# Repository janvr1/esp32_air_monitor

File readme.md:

### TO-DO:
* (SW) Ubidots

### Notes:
* GPIO 6-11: SPI flash
* GPIO 16-17: PSRAM
* GPIO 34-39: Input only
* EWMA filter: alpha = 2\*pi\*fc\*Ts/(1+2\*pi\*fc\*Ts)

### Display timings:
* F_pwm = 312,5 kHz (T=3,2 us)
* PWM: T_low@100%duty=~20 ns
* T_transfer = ~22 us (2 rows of 64 pixels * 3 colors)
* T_row = 200 us (T_transfer + 178 delay)
* Minimum brightness: T_on = 22 us (transfer time), T_off = 178 us (178 us delay)
* Maximum brightness: T_on = 200 us (22 us transfer + 178 us delay), T_off = 0 us
* Frame rate: 200..250 Hz (daylight), 100 Hz (nighttime)

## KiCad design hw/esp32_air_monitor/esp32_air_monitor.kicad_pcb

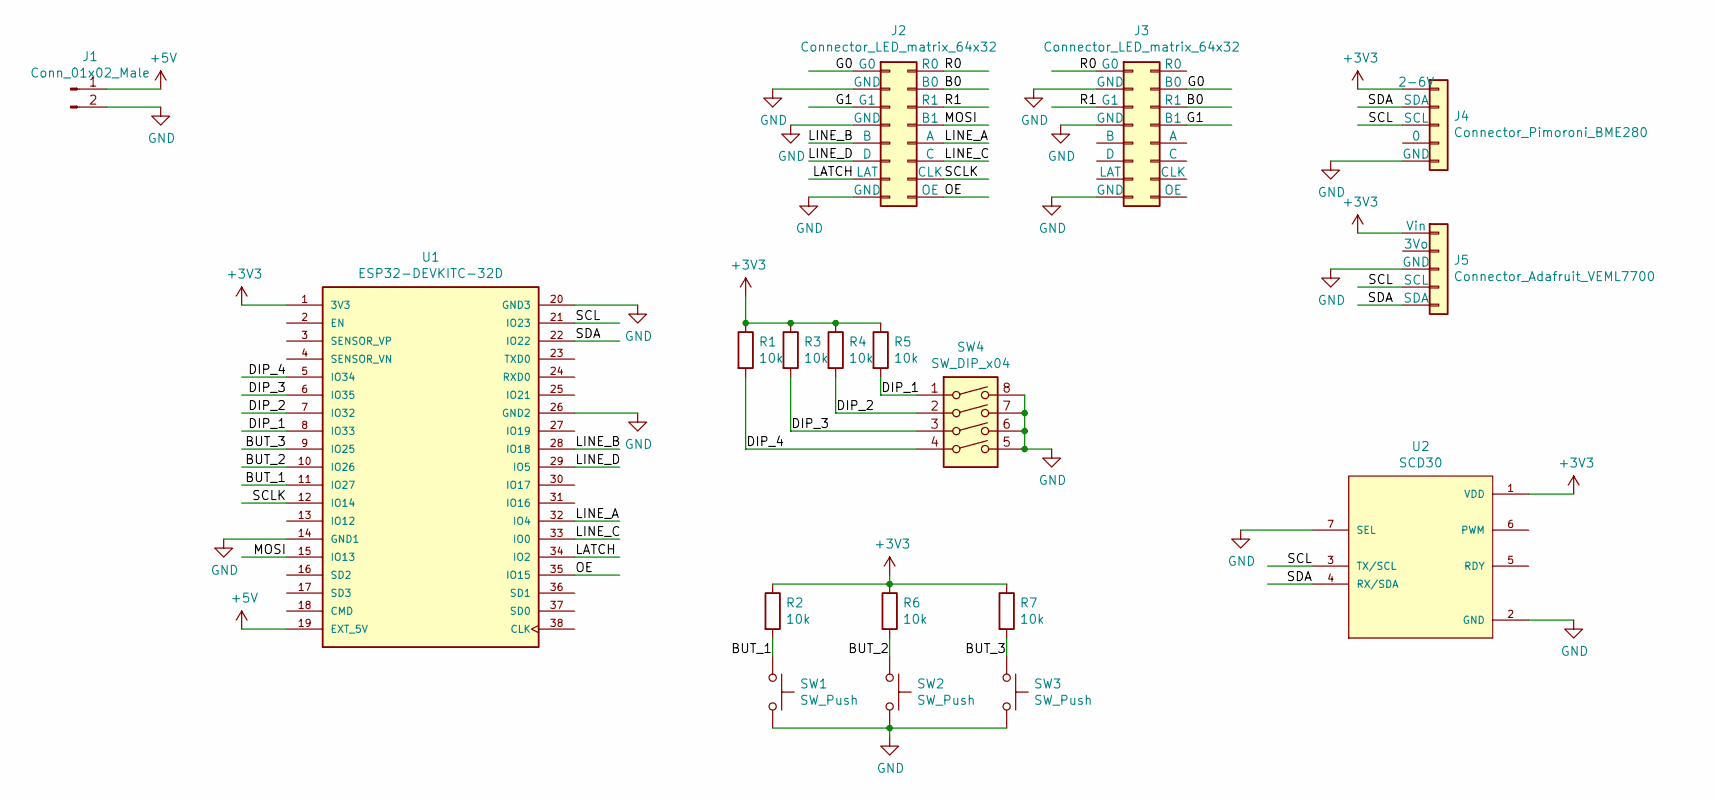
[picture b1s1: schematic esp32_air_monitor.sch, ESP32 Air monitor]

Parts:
J1: Conn_01x02_Male; PinHeader_1x02_P2.54mm_Vertical
J2, J3: Connector_LED_matrix_64x32
J4: Connector_Pimoroni_BME280
J5: Connector_Adafruit_VEML7700
R1, R2, R3, R4, R5, R6, R7: 10k; R_1206_3216Metric_Pad1.30x1.75mm_HandSolder
SW1, SW2, SW3: SW_Push; Push_Button_6x6mm
SW4: SW_DIP_x04; SW_DIP_SPSTx04_Slide_9.78x12.34mm_W7.62mm_P2.54mm
U1: ESP32-DEVKITC-32D; MODULE_ESP32-DEVKITC-32D; PARTREV 4
U2: SCD30; MODULE_SCD30; PARTREV D1

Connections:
+3V3: J4.1 (2-6V), J5.1 (Vin), R1.1, R2.1, R3.1, R4.1, R5.1, R6.1, R7.1, U1.1 (3V3), U2.1 (VDD)
+5V: J1.1, U1.19 (EXT_5V)
/B0: J2.4 (B0), J3.6 (R1)
/BUT_1: R2.2, SW1.1, U1.11 (IO27)
/BUT_2: R6.2, SW2.1, U1.10 (IO26)
/BUT_3: R7.2, SW3.1, U1.9 (IO25)
/DIP_1: R5.2, SW4.1, U1.8 (IO33)
/DIP_2: R4.2, SW4.2, U1.7 (IO32)
/DIP_3: R3.2, SW4.3, U1.6 (IO35)
/DIP_4: R1.2, SW4.4, U1.5 (IO34)
/G0: J2.1 (G0), J3.4 (B0)
/G1: J2.5 (G1), J3.8 (B1)
/LATCH: J2.13 (LAT), U1.34 (IO2)
/LINE_A: J2.10 (A), U1.32 (IO4)
/LINE_B: J2.9 (B), U1.28 (IO18)
/LINE_C: J2.12 (C), U1.33 (IO0)
/LINE_D: J2.11 (D), U1.29 (IO5)
/MOSI: J2.8 (B1), U1.15 (IO13)
/OE: J2.16 (OE), U1.35 (IO15)
/R0: J2.2 (R0), J3.1 (G0)
/R1: J2.6 (R1), J3.5 (G1)
/SCL: J4.3 (SCL), J5.4 (SCL), U1.21 (IO23), U2.3 (TX/SCL)
/SCLK: J2.14 (CLK), U1.12 (IO14)
/SDA: J4.2 (SDA), J5.5 (SDA), U1.22 (IO22), U2.4 (RX/SDA)
GND: J1.2, J2.3 (GND), J2.7 (GND), J2.15 (GND), J3.3 (GND), J3.7 (GND), J3.15 (GND), J4.5 (GND), J5.3 (GND), SW1.2, SW2.2, SW3.2, SW4.5, SW4.6, SW4.7, SW4.8, U1.14 (GND1), U1.20 (GND3), U1.26 (GND2), U2.2 (GND), U2.7 (SEL)

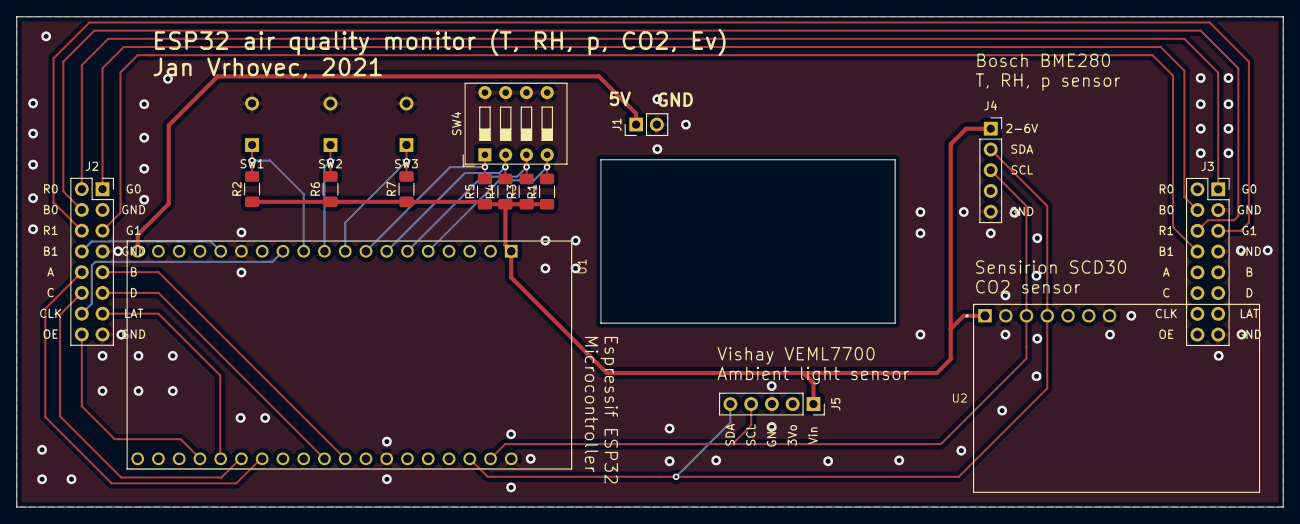
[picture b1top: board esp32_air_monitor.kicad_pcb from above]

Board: 2 copper layers, 155.0 x 60.0 mm, 18 parts (0 on the bottom side), 25 nets.

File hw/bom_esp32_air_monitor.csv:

"Id";"Designator";"Package";"Quantity";"Designation";"Supplier and ref";
1;"U1";"MODULE_ESP32-DEVKITC-32D";1;"ESP32-DEVKITC-32D";;;
2;"U2";"MODULE_SCD30";1;"SCD30";;;
3;"J2,J3";"Connector_LED_matrix_64x32";2;"Connector_LED_matrix_64x32";;;
4;"J5";"Connector_Adafruit_VEML7700";1;"Connector_Adafruit_VEML7700";;;
5;"J4";"Connector_Pimoroni_BME280";1;"Connector_Pimoroni_BME280";;;
6;"J1";"PinHeader_1x02_P2.54mm_Vertical";1;"Conn_01x02_Male";;;

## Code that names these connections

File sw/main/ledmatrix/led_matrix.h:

#ifndef JAN_LEDMATRIX_H
#define JAN_LEDMATRIX_H
#include <driver/gpio.h>
#include <driver/spi_master.h>

#define LM_WIDTH 64
#define LM_HEIGHT 32

typedef enum lm_color
{
    LM_COLOR_RED = 0x00,
    LM_COLOR_GREEN = 0x01,
    LM_COLOR_BLUE = 0x02,
} lm_color_t;

typedef struct led_matrix
{
    gpio_num_t line_A;
    gpio_num_t line_B;
    gpio_num_t line_C;
    gpio_num_t line_D;
    gpio_num_t output_enable;
    gpio_num_t latch;
    uint8_t *frame;
    bool ready;
    bool tx_in_progress;
    uint16_t duty;
    spi_device_handle_t spidev;

} led_matrix_t;

esp_err_t lm_init(led_matrix_t *lm,
                  gpio_num_t A,
                  gpio_num_t B,
                  gpio_num_t C,
                  gpio_num_t D,
                  gpio_num_t output_enable,
                  gpio_num_t latch);
esp_err_t lm_deinit(led_matrix_t *lm);
esp_err_t lm_show_frame(led_matrix_t *lm);
void lm_set_duty(led_matrix_t *lm, uint16_t duty);
void lm_set_pixel(led_matrix_t *lm, int val, int x, int y, lm_color_t c);
void lm_draw_char(led_matrix_t *lm, unsigned char chr, int row, int pos, lm_color_t c);
esp_err_t lm_draw_text(led_matrix_t *lm, char *text, int row, int pos, lm_color_t c);
void lm_clear_frame(led_matrix_t *lm);
#endif

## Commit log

2020-12-26 Initial commit. +Hardware files
2021-01-08 Added software section :)
2021-01-09 Added VEML7700 driver, improved SCD30 and BME280 drivers
2021-01-10 Added webserver, other improvements
2021-01-12 Big improvements, huge! The best commit in the history of commits, maybe ever.
2021-01-13 Dodan led matrix display Dodana sinhronizacija časa prek sntpm, Dodan prikaz IP-ja ob prižigu
2021-01-16 Project restructuring
2021-01-16 Remove DMA for SPI transactions
2021-01-17 Update ledmatrix driver
2021-01-23 Update PCB
2021-02-01 Fix hardware bug (SCL pin), patch software for new hw revision
2021-02-13 Change some types in web_app.c
2021-02-14 Try to reconnect every 30 seconds in case of lost wifi connetction
2023-05-04 Bugfix for wifi in AP mode Update to ESP-IDF v5
2023-05-04 New version of components
